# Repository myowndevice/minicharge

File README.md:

## Мини зарядное устройство для литиевого аккумулятора

Это мини устройство позволяет зарядить один литиевый аккумулятор от micro USB разъёма. Несложная пайка. Позволяет познакомиться с основами микроэлектроники, научиться паять SMD компоненты. Это устройство принесёт вам большую пользу как дома, так и в приборостроении.
С его помощью можно восстановить аккумулятор «ушедший» в глубокий разряд, зарядить запасной аккумулятор сотового телефона, зарядить аккумуляторы таблетки LIR2030 и аналогичные, а также любой аккумулятор в широко распространнёном размере 18650 или любом другом.

Основные параметры:
- Ток заряда — 40мА, 120мА, 600мА
- Компактный размер
- Работа с любыми аккумуляторами типа Li-pol, Li-ion (напряжение заряда 4.2В)
- Питание по проводу microusb от компьютера или любого зарядного устройства телефона
- Защита от переплюсовки аккумулятора
- Светодиодный индикатор окончания заряда
    
Данный репозитарий содержит все необходимые файлы для изготовления зарядного устройства.Если вы будете скачивать файлы через web не забудьте скачать общую папку Kicadlib.

Ознакомится со схемой и подробным описанием мини зарядного устройства и порядка сборки можно, [прочитав эту подробную статью](http://myowndevice.ru/index.php/pribory/instrumenty-i-izmeritelnye-pribory/item/51-mini-zaryadnoe-ustrojstvo)

Также [здесь](http://myowndevice.ru) вы найдете подробное описание как сделать другие приборы, много теории о том, как их делать, методику изготовления печатных плат и много другого.

Изучай микроконтроллеры, делай платы дома, разрабатывай электронику сам!

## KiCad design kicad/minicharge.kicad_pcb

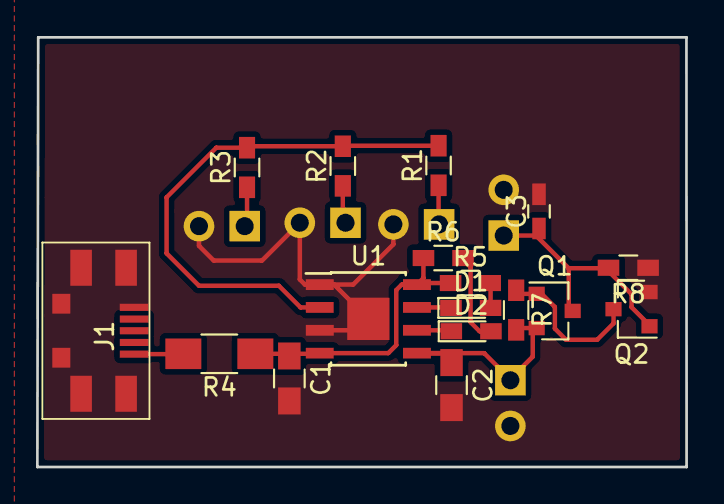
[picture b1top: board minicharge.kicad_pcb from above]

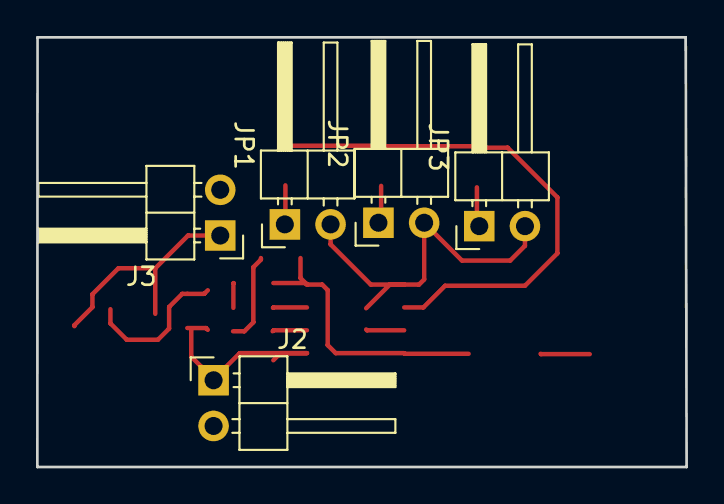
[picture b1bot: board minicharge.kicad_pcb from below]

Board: 2 copper layers, 36.1 x 23.9 mm, 22 parts (5 on the bottom side), 14 nets.

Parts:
C1, C2: 10u; C_0805_HandSoldering
C3: 100n; C_0603_HandSoldering
D1, D2: LED; LED_0603_HandSoldering
J1: USB_OTG; usb5s_flip
J2: BAT2; Pin_Header_Angled_1x02_Pitch2.54mm
J3: BAT; Pin_Header_Angled_1x02_Pitch2.54mm
JP1, JP2, JP3: Jumper_NO_Small; Pin_Header_Angled_1x02_Pitch2.54mm
Q1: IRLML6402; SOT-23
Q2: irlml2502; SOT-23
R1: 30k; R_0603_HandSoldering
R2: 10k; R_0603_HandSoldering
R3: 2k; R_0603_HandSoldering
R4: 0R5; R_1206_HandSoldering
R5, R6: 1k; R_0603_HandSoldering
R7, R8: 100k; R_0603_HandSoldering
U1: TP4056; SOIC-8-1EP_3.9x4.9mm_Pitch1.27mm

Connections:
/prog: R1.2, R2.2, R3.2, U1.2
/vin: C1.1, R4.1, R5.1, R6.1, U1.4, U1.8
GND: C1.2, C2.2, C3.2, J1.5, J2.2, J3.2, JP1.2, JP2.2, JP3.2, Q2.2, R8.1, U1.1, U1.3, U1.9
unnamed: C2.1, J2.1, Q1.2, R7.2, U1.5
unnamed: C3.1, J3.1, Q1.3, Q2.1, R8.2
unnamed: D1.1, U1.7
unnamed: D1.2, R5.2
unnamed: D2.1, U1.6
unnamed: D2.2, R6.2
unnamed: J1.1, R4.2
unnamed: JP1.1, R1.1
unnamed: JP2.1, R2.1
unnamed: JP3.1, R3.1
unnamed: Q1.1, Q2.3, R7.1

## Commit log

2020-12-18 start
